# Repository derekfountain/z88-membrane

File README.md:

# A new keyboard membrane for the Z88 laptop

The Z88 laptop from 1988 is well out of support. :)
I have a couple of them, and although they're working fine, I've
always been a bit nervous of that keyboard membrane. Membranes on
machines like the ZX Spectrum have a finite life and need replacing
every so often. Would the Z88's keyboard membrane be the same?

I decided to create a new one using a flexi-PCB. I wasn't sure if this
approach would work, but I wanted to find out. So, with considerable
help from my friend Andrew Menadue, I made one. Here it is:

The original is the red one, the new one, as created by JLCPCB, is the
orange one.

The photo is of v1.1, which has the keyboard tails. v1.0 didn't have those,
which was a bit of an oversight. There are no stiffners on the tails. I
didn't know how to create them. It works without stiffners, but
you need to hold the tail right up at the gold fingers and wiggle it into
the connector. Stiffners will be added to v1.2, should I make one.

It works well, sitting perfectly in place under the Z88 rubber mat, and
conducting the carbon under-surface just as expected.

I had mine made from 0.2mm flexi-PCB, which is as thick as JLCPCB can make
them. It could stand being a bit thicker, if possible. It's a little bit
floppy compared to the original one.

[Derek Fountain](https://www.derekfountain.org/), November 2025

# Acknowledgements

[Andrew Menadue](http://trochilidae.blogspot.com/) for doing the clever
KiCAD footprint thing and the original layout of the keys.

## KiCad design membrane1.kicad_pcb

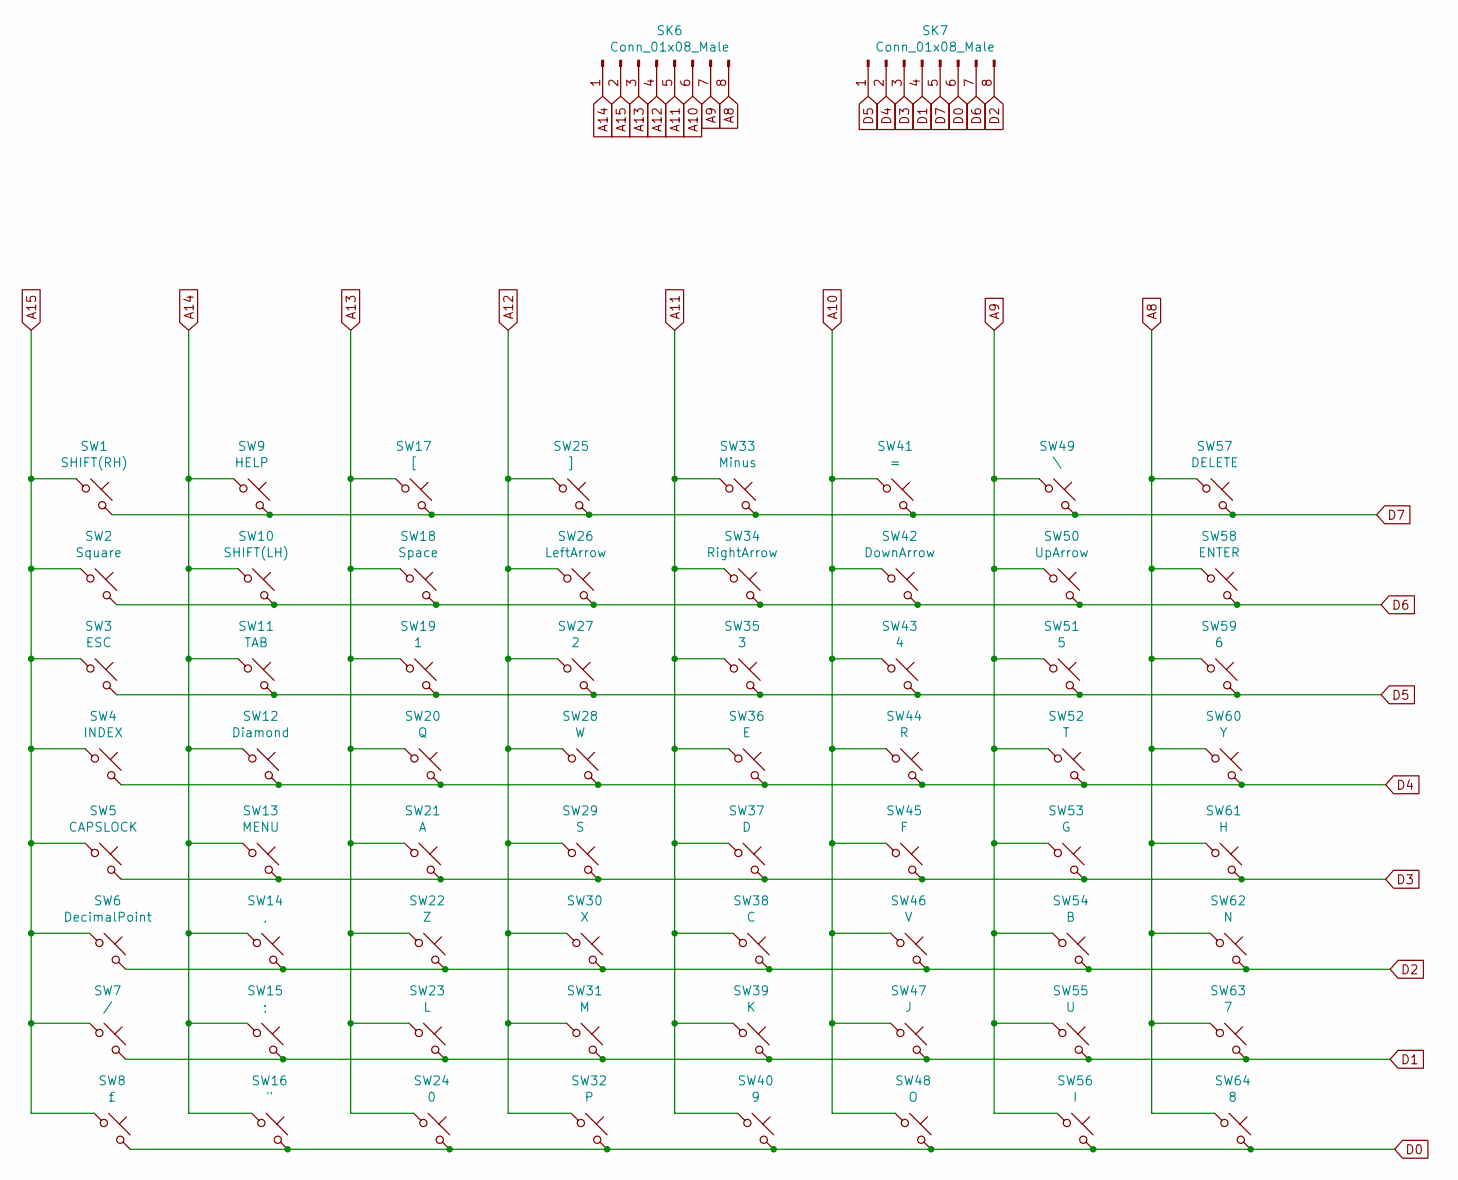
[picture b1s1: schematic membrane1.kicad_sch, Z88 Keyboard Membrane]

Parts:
SK6, SK7: Conn_01x08_Male; PinSocket_1x08_P2.00mm_Vertical_SMD_Pin1Left
SW1: SHIFT(RH); z88_shiftrh_pad1
SW2: Square; z88_pad1
SW3: ESC; z88_pad1
SW4: INDEX; z88_pad1
SW5: CAPSLOCK; z88_pad1
SW6: DecimalPoint; z88_pad1
SW7: /; z88_pad1
SW8: £; z88_pad1
SW9: HELP; z88_pad1
SW10: SHIFT(LH); z88_shiftlh_pad1
SW11: TAB; z88_tab_pad1
SW12: Diamond; z88_shiftrh_pad1
SW13: MENU; z88_pad1
SW14: ,; z88_pad1
SW15: ;; z88_pad1
SW16: "; z88_pad1
SW17: [; z88_pad1
SW18: Space; z88_space_pad1
SW19: 1; z88_pad1
SW20: Q; z88_pad1
SW21: A; z88_pad1
SW22: Z; z88_pad1
SW23: L; z88_pad1
SW24: 0; z88_pad1
SW25: ]; z88_pad1
SW26: LeftArrow; z88_pad1
SW27: 2; z88_pad1
SW28: W; z88_pad1
SW29: S; z88_pad1
SW30: X; z88_pad1
SW31: M; z88_pad1
SW32: P; z88_pad1
SW33: Minus; z88_pad1
SW34: RightArrow; z88_pad1
SW35: 3; z88_pad1
SW36: E; z88_pad1
SW37: D; z88_pad1
SW38: C; z88_pad1
SW39: K; z88_pad1
SW40: 9; z88_pad1
SW41: =; z88_pad1
SW42: DownArrow; z88_pad1
SW43: 4; z88_pad1
SW44: R; z88_pad1
SW45: F; z88_pad1
SW46: V; z88_pad1
SW47: J; z88_pad1
SW48: O; z88_pad1
SW49: \; z88_pad1
SW50: UpArrow; z88_pad1
SW51: 5; z88_pad1
SW52: T; z88_pad1
SW53: G; z88_pad1
SW54: B; z88_pad1
SW55: U; z88_pad1
SW56: I; z88_pad1
SW57: DELETE; z88_pad1
SW58: ENTER; z88_enter_pad1
SW59: 6; z88_pad1
SW60: Y; z88_pad1
SW61: H; z88_pad1
SW62: N; z88_pad1
SW63: 7; z88_pad1
SW64: 8; z88_pad1

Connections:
A8: SK6.8, SW57.1, SW58.1, SW59.1, SW60.1, SW61.1, SW62.1, SW63.1, SW64.1
A9: SK6.7, SW49.1, SW50.1, SW51.1, SW52.1, SW53.1, SW54.1, SW55.1, SW56.1
A10: SK6.6, SW41.1, SW42.1, SW43.1, SW44.1, SW45.1, SW46.1, SW47.1, SW48.1
A11: SK6.5, SW33.1, SW34.1, SW35.1, SW36.1, SW37.1, SW38.1, SW39.1, SW40.1
A12: SK6.4, SW25.1, SW26.1, SW27.1, SW28.1, SW29.1, SW30.1, SW31.1, SW32.1
A13: SK6.3, SW17.1, SW18.1, SW19.1, SW20.1, SW21.1, SW22.1, SW23.1, SW24.1
A14: SK6.1, SW9.1, SW10.1, SW11.1, SW12.1, SW13.1, SW14.1, SW15.1, SW16.1
A15: SK6.2, SW1.1, SW2.1, SW3.1, SW4.1, SW5.1, SW6.1, SW7.1, SW8.1
D0: SK7.6, SW8.2, SW16.2, SW24.2, SW32.2, SW40.2, SW48.2, SW56.2, SW64.2
D1: SK7.4, SW7.2, SW15.2, SW23.2, SW31.2, SW39.2, SW47.2, SW55.2, SW63.2
D2: SK7.8, SW6.2, SW14.2, SW22.2, SW30.2, SW38.2, SW46.2, SW54.2, SW62.2
D3: SK7.3, SW5.2, SW13.2, SW21.2, SW29.2, SW37.2, SW45.2, SW53.2, SW61.2
D4: SK7.2, SW4.2, SW12.2, SW20.2, SW28.2, SW36.2, SW44.2, SW52.2, SW60.2
D5: SK7.1, SW3.2, SW11.2, SW19.2, SW27.2, SW35.2, SW43.2, SW51.2, SW59.2
D6: SK7.7, SW2.2, SW10.2, SW18.2, SW26.2, SW34.2, SW42.2, SW50.2, SW58.2
D7: SK7.5, SW1.2, SW9.2, SW17.2, SW25.2, SW33.2, SW41.2, SW49.2, SW57.2

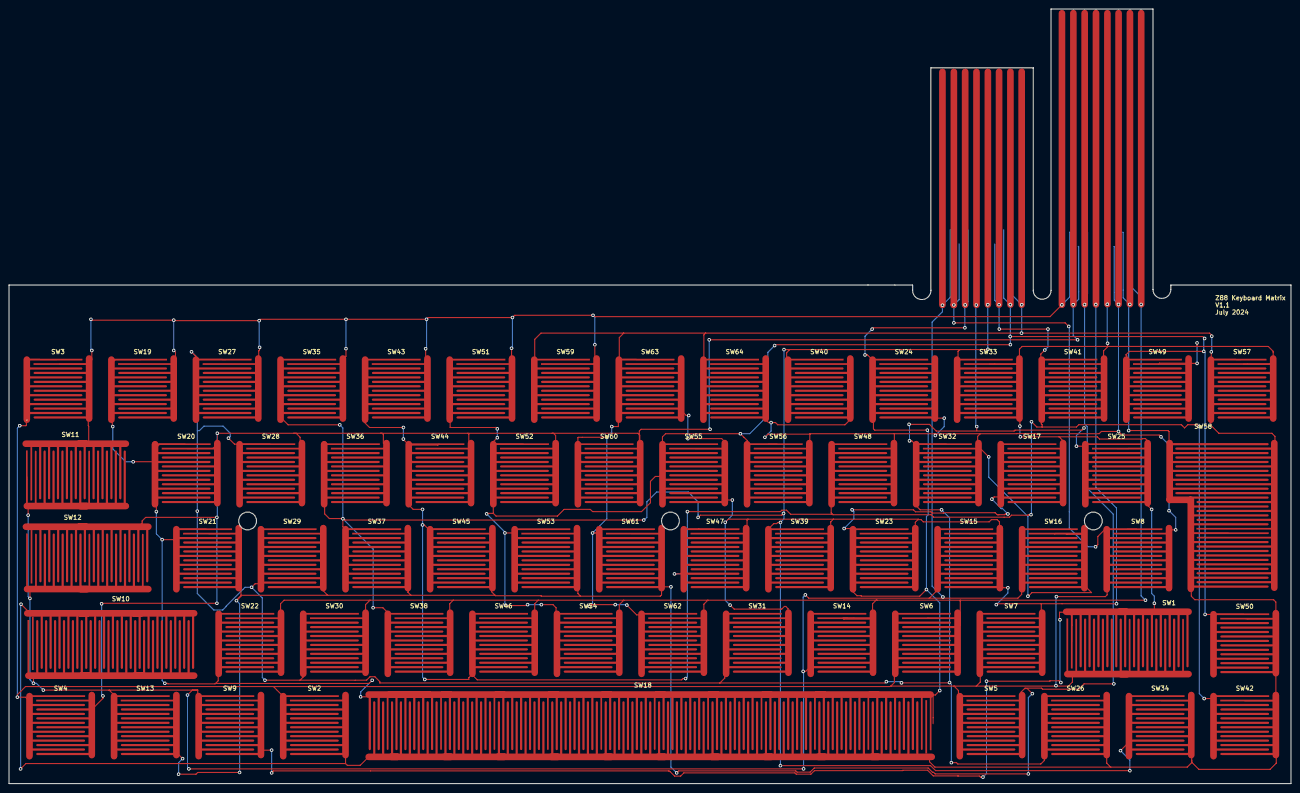
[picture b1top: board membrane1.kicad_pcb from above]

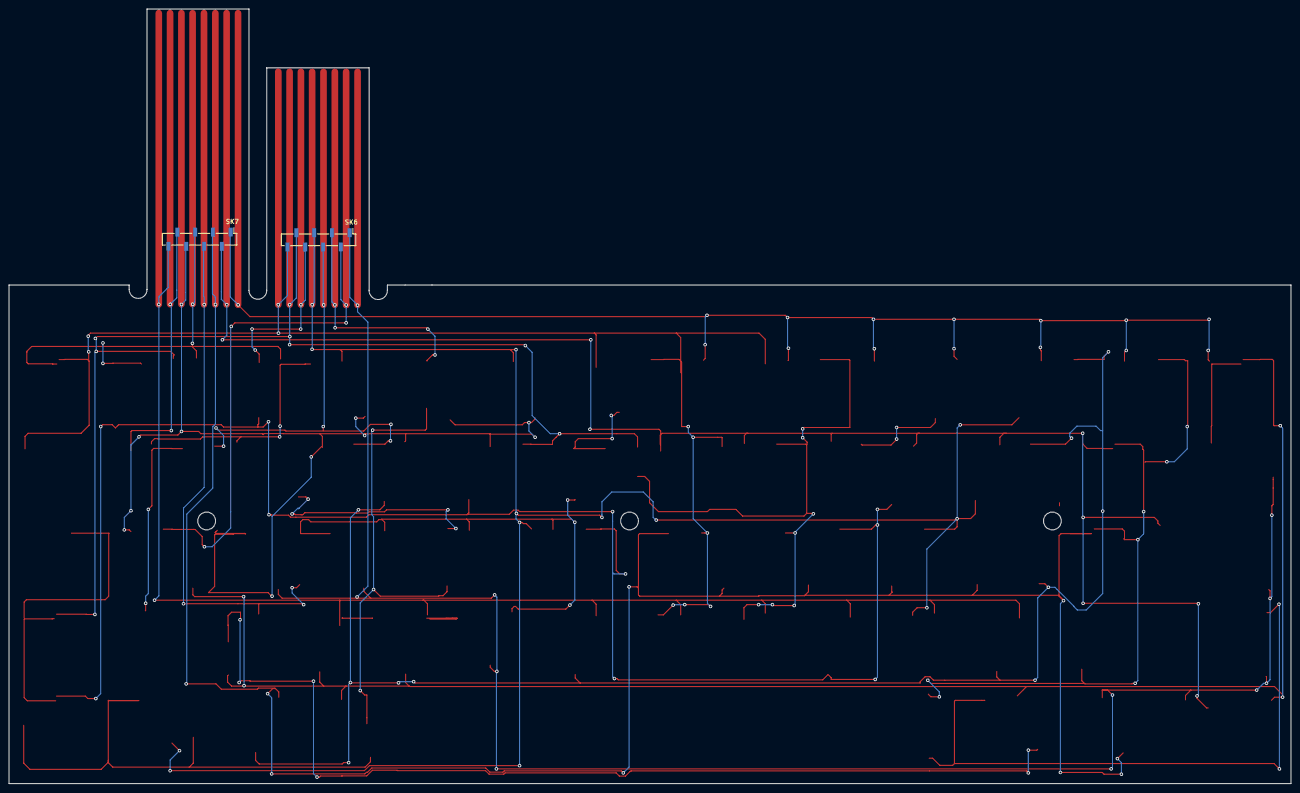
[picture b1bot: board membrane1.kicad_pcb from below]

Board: 2 copper layers, 288.0 x 174.0 mm, 66 parts (2 on the bottom side), 16 nets.

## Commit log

2025-11-10 v1.1 added
2025-11-10 add readme
